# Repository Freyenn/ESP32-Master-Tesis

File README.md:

## PCB Designed for Master's Tesis

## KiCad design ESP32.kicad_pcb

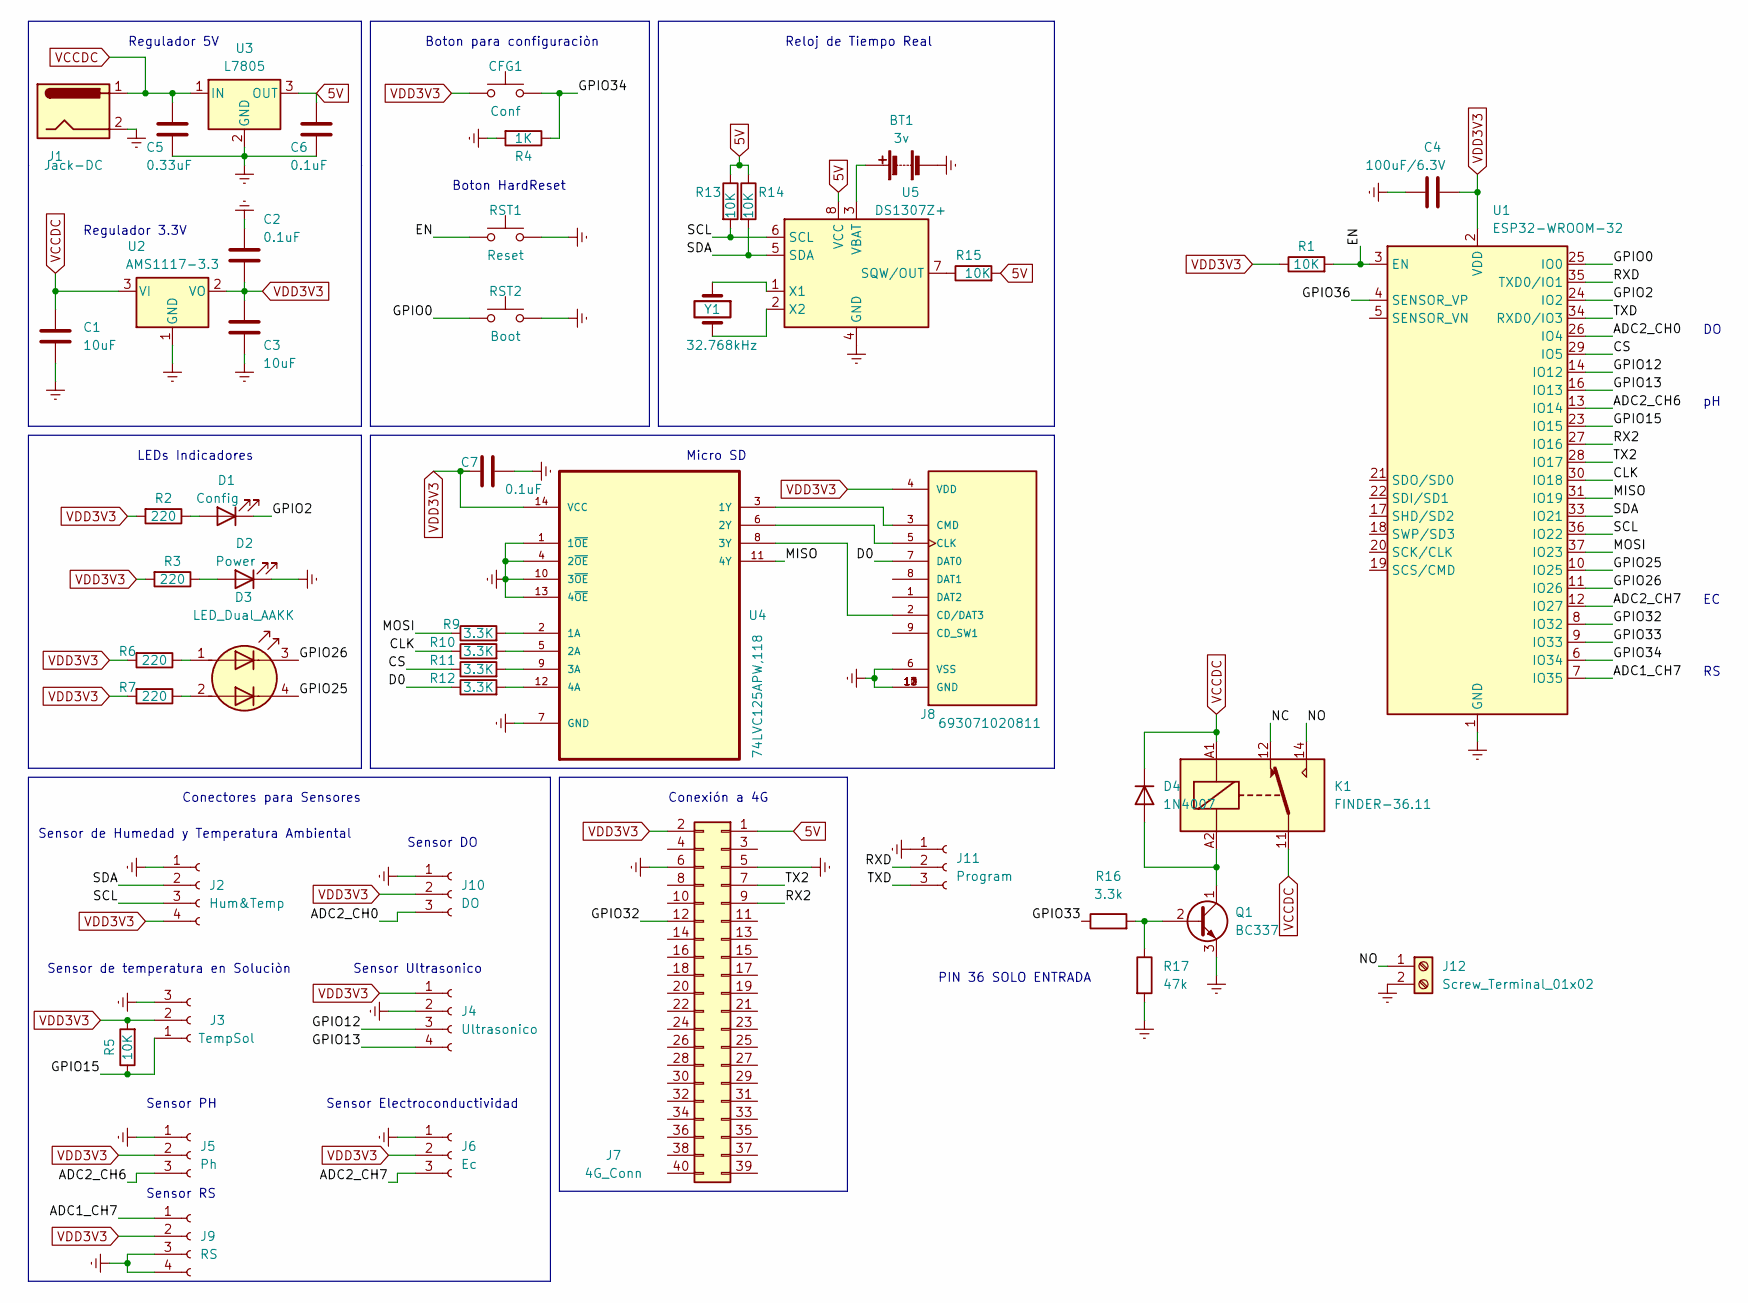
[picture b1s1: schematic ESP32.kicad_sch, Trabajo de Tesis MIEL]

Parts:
BT1: 3v; S8421-45R_1
C1, C3: 10uF; C_1210_3225Metric_Pad1.33x2.70mm_HandSolder
C2, C6, C7: 0.1uF; C_0805_2012Metric_Pad1.18x1.45mm_HandSolder
C4: 100uF/6.3V; C_1210_3225Metric_Pad1.33x2.70mm_HandSolder
C5: 0.33uF; C_0805_2012Metric_Pad1.18x1.45mm_HandSolder
CFG1: Conf; SW_Tactile_SPST_Angled_PTS645Vx83-2LFS
D1: Config; LED_1206_3216Metric_Pad1.42x1.75mm_HandSolder
D2: Power; LED_1206_3216Metric_Pad1.42x1.75mm_HandSolder
D3: LED_Dual_AAKK; LED_RGB_1210
D4: 1N4007; D_DO-41_SOD81_P10.16mm_Horizontal
J1: Jack-DC; BarrelJack_Horizontal
J2: Hum&Temp; JST_EH_S4B-EH_1x04_P2.50mm_Horizontal
J3: TempSol; JST_EH_S3B-EH_1x03_P2.50mm_Horizontal
J4: Ultrasonico; JST_EH_S4B-EH_1x04_P2.50mm_Horizontal
J5: Ph; JST_EH_B3B-EH-A_1x03_P2.50mm_Vertical
J6: Ec; JST_EH_B3B-EH-A_1x03_P2.50mm_Vertical
J7: 4G_Conn; PinHeader_2x20_P2.54mm_Vertical
J8: 693071020811
J9: RS; RJ12_Amphenol_54601
J10: DO; JST_EH_B3B-EH-A_1x03_P2.50mm_Vertical
J11: Program; PinHeader_1x03_P2.54mm_Vertical
J12: Screw_Terminal_01x02; TerminalBlock_bornier-2_P5.08mm
K1: FINDER-36.11; Relay_SPDT_Finder_36.11
Q1: BC337; TO-92_Inline
R1, R5, R13, R14, R15: 10K; R_0805_2012Metric_Pad1.20x1.40mm_HandSolder
R2, R3, R6, R7: 220; R_0805_2012Metric_Pad1.20x1.40mm_HandSolder
R4: 1K; R_0805_2012Metric_Pad1.20x1.40mm_HandSolder
R9, R10, R11, R12: 3.3K; R_0805_2012Metric_Pad1.20x1.40mm_HandSolder
R16: 3.3k; R_0805_2012Metric_Pad1.20x1.40mm_HandSolder
R17: 47k; R_0805_2012Metric_Pad1.20x1.40mm_HandSolder
RST1: Reset; SW_Tactile_SPST_Angled_PTS645Vx83-2LFS
RST2: Boot; SW_SPST_B3U-1000P
U1: ESP32-WROOM-32
U2: AMS1117-3.3; SOT-223-3_TabPin2
U3: L7805; TO-251-3_Vertical
U4: 74LVC125APW,118; SOP65P640X110-14N
U5: DS1307Z+; SOIC-8_3.9x4.9mm_P1.27mm
Y1: 32.768kHz; Crystal_AT310_D3.0mm_L10.0mm_Horizontal

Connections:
5V: C6.1, J7.1, R13.1, R14.1, R15.2, U3.3 (OUT), U5.8 (VCC)
/ADC1_CH7: J9.1, U1.7 (IO35)
/ADC2_CH0: J10.3, U1.26 (IO4)
/ADC2_CH6: J5.3, U1.13 (IO14)
/ADC2_CH7: J6.3, U1.12 (IO27)
/CLK: R10.1, U1.30 (IO18)
/CS: R11.1, U1.29 (IO5)
/D0: J8.7 (DAT0), R12.1
/EN: R1.2, RST1.1, U1.3 (EN)
/GPIO0: RST2.1, U1.25 (IO0)
/GPIO2: D1.1 (K), U1.24 (IO2)
/GPIO12: J4.3, U1.14 (IO12)
/GPIO13: J4.4, U1.16 (IO13)
/GPIO15: J3.1, R5.1, U1.23 (IO15)
/GPIO25: D3.4 (K2), U1.10 (IO25)
/GPIO26: D3.3 (K1), U1.11 (IO26)
/GPIO32: J7.12, U1.8 (IO32)
/GPIO33: R16.1, U1.9 (IO33)
/GPIO34: CFG1.2, R4.1, U1.6 (IO34)
/GPIO36: U1.4 (SENSOR_VP)
/MISO: U1.31 (IO19), U4.11 (4Y)
/MOSI: R9.1, U1.37 (IO23)
/NC: K1.12
/NO: J12.1, K1.14
/RX2: J7.9, U1.27 (IO16)
/RXD: J11.2, U1.35 (TXD0/IO1)
/SCL: J2.3, R13.2, U1.36 (IO22), U5.6 (SCL)
/SDA: J2.2, R14.2, U1.33 (IO21), U5.5 (SDA)
/TX2: J7.7, U1.28 (IO17)
/TXD: J11.3, U1.34 (RXD0/IO3)
Earth: BT1.2 (-), C1.2, C2.1, C3.2, C4.1, C5.2, C6.2, C7.2, D2.1 (K), J1.2, J2.1, J3.3, J4.2, J5.1, J6.1, J7.5, J7.6, J8.6 (VSS), J8.10 (GND), J8.11 (GND), J8.12 (GND), J8.13 (GND), J9.3, J9.4, J10.1, J11.1, J12.2, Q1.3 (E), R4.2, R17.2, RST1.2, RST2.2, U1.1 (GND), U1.15 (GND), U1.38 (GND), U1.39 (GND), U2.1 (GND), U3.2 (GND), U4.1 (1~OE), U4.4 (2~OE), U4.7 (GND), U4.10 (3~OE), U4.13 (4~OE), U5.4 (GND)
unnamed: BT1.1 (+), U5.3 (VBAT)
unnamed: D1.2 (A), R2.1
unnamed: D2.2 (A), R3.1
unnamed: D3.1 (A1), R6.1
unnamed: D3.2 (A2), R7.1
unnamed: D4.2 (A), K1.A2, Q1.1 (C)
unnamed: J8.2 (CD/DAT3), U4.8 (3Y)
unnamed: J8.3 (CMD), U4.3 (1Y)
unnamed: J8.5 (CLK), U4.6 (2Y)
unnamed: Q1.2 (B), R16.2, R17.1
unnamed: R9.2, U4.2 (1A)
unnamed: R10.2, U4.5 (2A)
unnamed: R11.2, U4.9 (3A)
unnamed: R12.2, U4.12 (4A)
unnamed: R15.1, U5.7 (SQW/OUT)
unnamed: U5.1 (X1), Y1.1
unnamed: U5.2 (X2), Y1.2
VCCDC: C1.1, C5.1, D4.1 (K), J1.1, K1.11, K1.A1, U2.3 (VI), U3.1 (IN)
VDD3V3: C2.2, C3.1, C4.2, C7.1, CFG1.1, J2.4, J3.2, J4.1, J5.2, J6.2, J7.2, J8.4 (VDD), J9.2, J10.2, R1.1, R2.2, R3.2, R5.2, R6.2, R7.2, U1.2 (VDD), U2.2 (VO), U4.14 (VCC)

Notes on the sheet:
Sensor Ultrasonico
PIN 36 SOLO ENTRADA
Sensor Electroconductividad
Sensor de temperatura en Soluciòn
Reloj de Tiempo Real
Boton para configuraciòn
Sensor DO
Boton HardReset
LEDs Indicadores
Sensor RS
Sensor de Humedad y Temperatura Ambiental
Micro SD
Sensor PH
Conexión a 4G
Conectores para Sensores
Regulador 3.3V
Regulador 5V

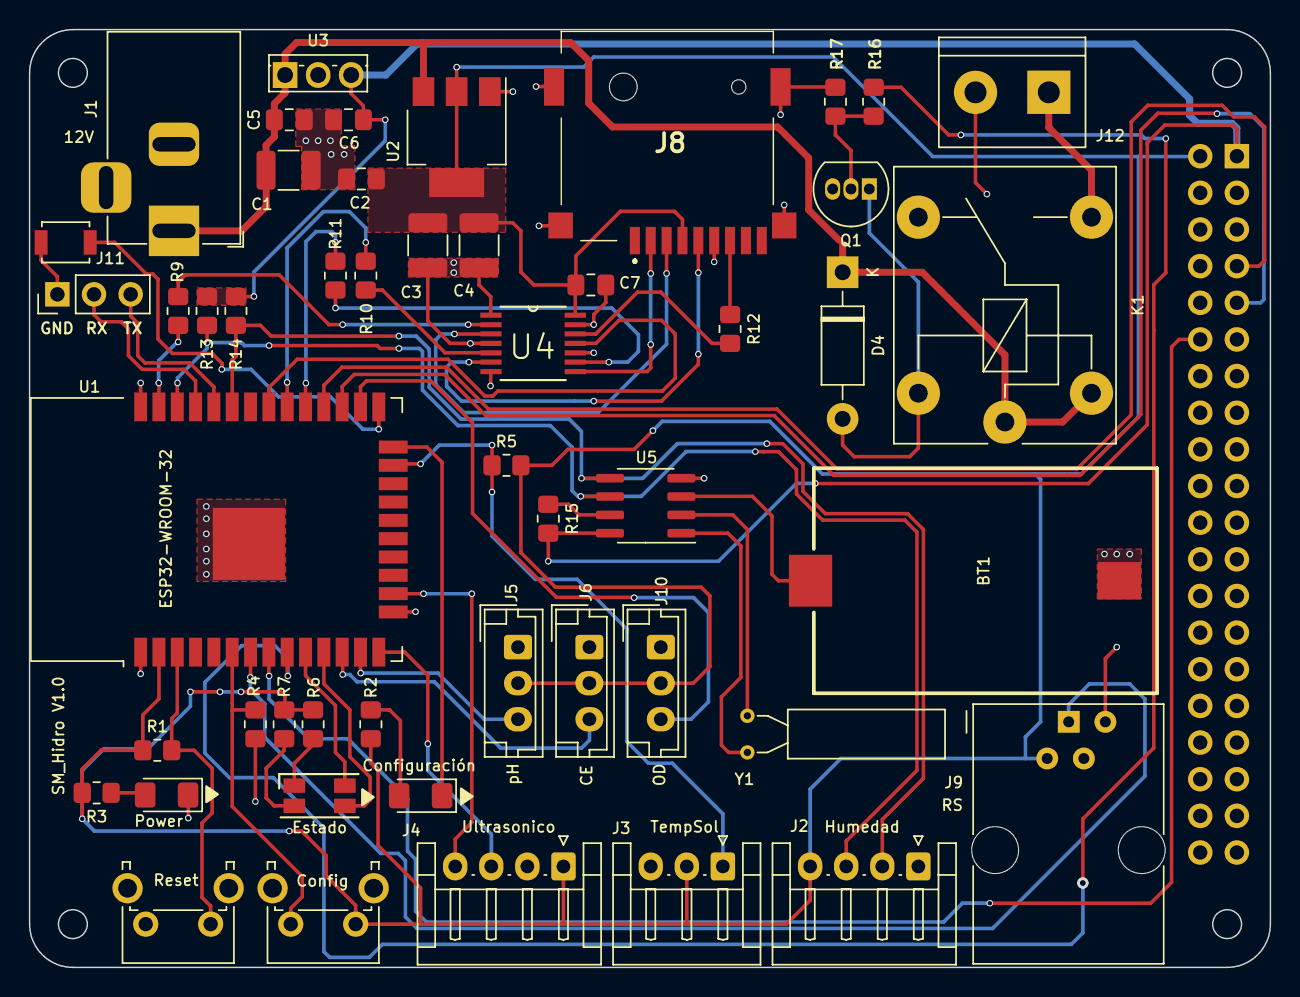
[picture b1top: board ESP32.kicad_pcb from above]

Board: 2 copper layers, 86.0 x 65.0 mm, 51 parts (1 on the bottom side), 48 nets.
